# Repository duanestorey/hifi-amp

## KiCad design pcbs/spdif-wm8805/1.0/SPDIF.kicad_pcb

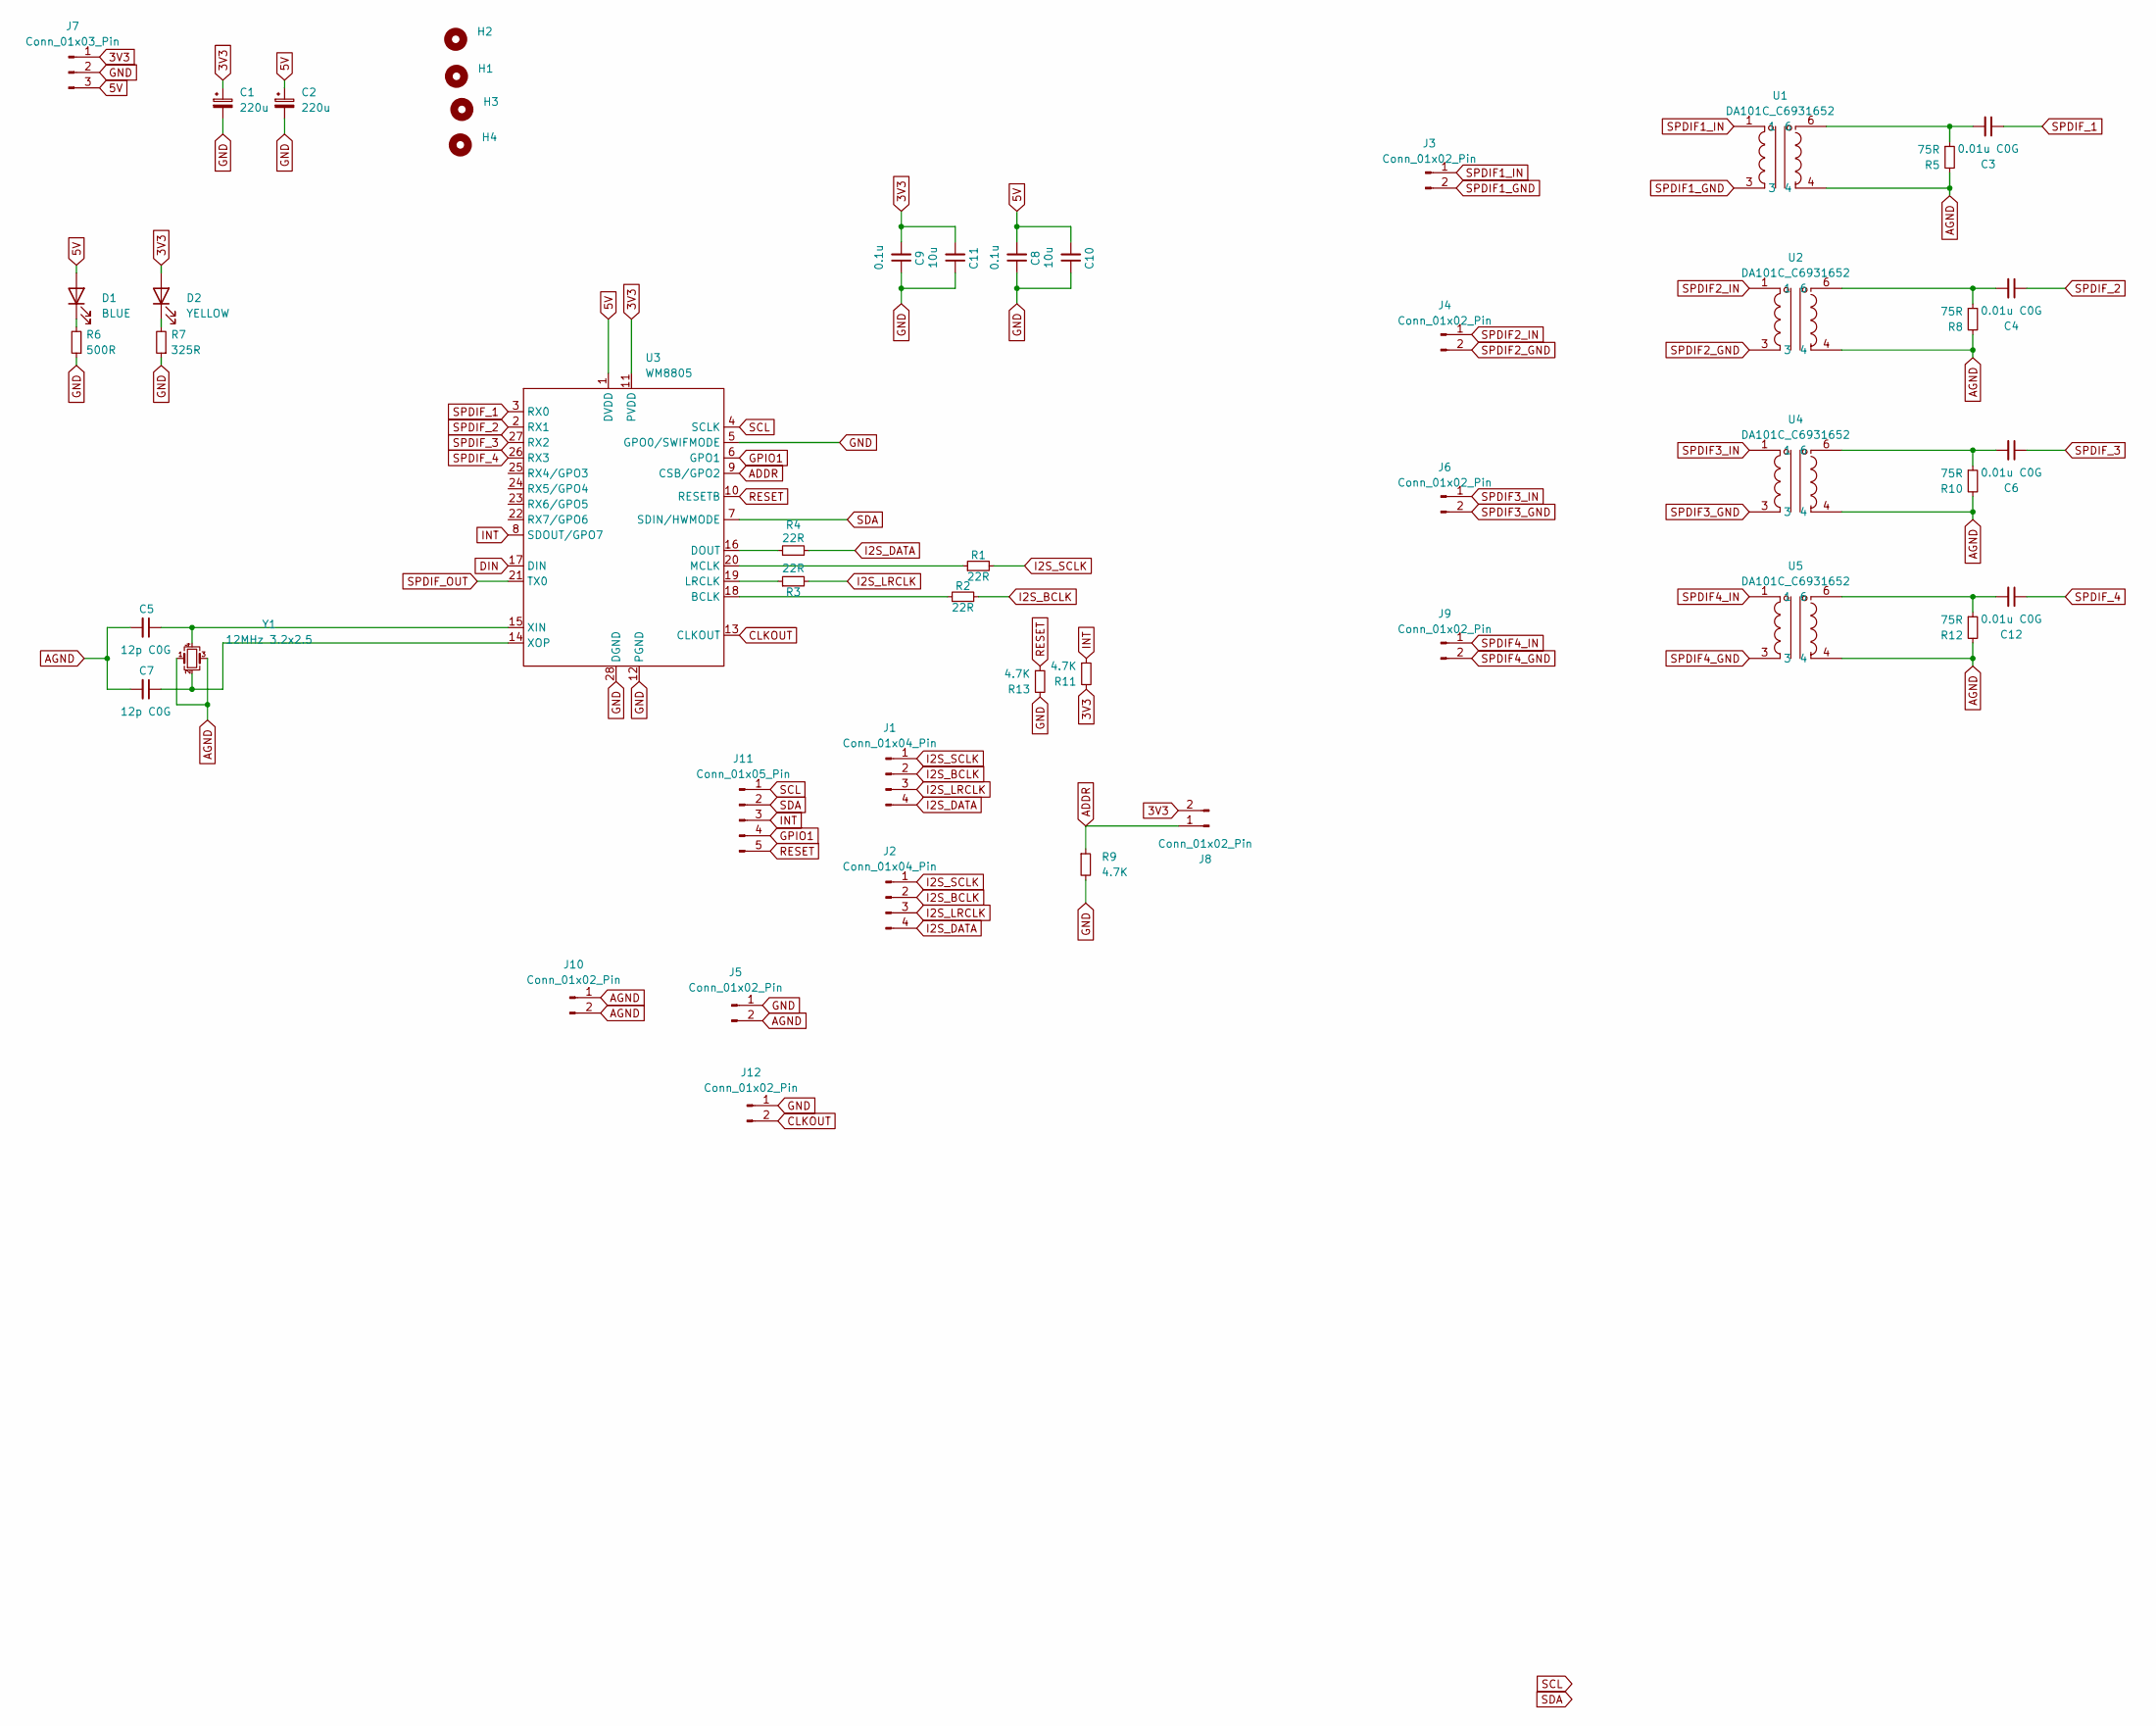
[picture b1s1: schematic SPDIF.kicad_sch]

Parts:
C1, C2: 220u; CP_Radial_D6.3mm_P2.50mm
C3, C4, C6, C12: 0.01u C0G; C_0805_2012Metric_Pad1.18x1.45mm_HandSolder; Mouser 791-0805N103G250CT
C5, C7: 12p C0G; C_0805_2012Metric_Pad1.18x1.45mm_HandSolder; Mouser 603-CC805FRNPO9BN120
C8, C9: 0.1u; C_0805_2012Metric_Pad1.18x1.45mm_HandSolder
C10, C11: 10u; C_1206_3216Metric_Pad1.33x1.80mm_HandSolder
D1: BLUE; LED_0805_2012Metric_Pad1.15x1.40mm_HandSolder
D2: YELLOW; LED_0805_2012Metric_Pad1.15x1.40mm_HandSolder
H1, H2, H3, H4: MountingHole; MountingHole_3.2mm_M3_DIN965_Pad_TopOnly
J1: Conn_01x04_Pin; JST_PH_B4B-PH-K_1x04_P2.00mm_Vertical
J2: Conn_01x04_Pin; PinHeader_1x04_P2.54mm_Vertical
J3, J4, J6, J9: Conn_01x02_Pin; JST_XH_B2B-XH-A_1x02_P2.50mm_Vertical
J5, J8, J12: Conn_01x02_Pin; PinHeader_1x02_P2.54mm_Vertical
J7: Conn_01x03_Pin; JST_PH_B3B-PH-K_1x03_P2.00mm_Vertical
J10: Conn_01x02_Pin; JST_PH_B2B-PH-K_1x02_P2.00mm_Vertical
J11: Conn_01x05_Pin; JST_PH_B5B-PH-K_1x05_P2.00mm_Vertical
R1, R2, R3, R4: 22R; R_0805_2012Metric_Pad1.20x1.40mm_HandSolder
R5, R8, R10, R12: 75R; R_0805_2012Metric_Pad1.20x1.40mm_HandSolder; Mouser 71-CRCW0603-75-E3
R6: 500R; R_0603_1608Metric_Pad0.98x0.95mm_HandSolder
R7: 325R; R_0603_1608Metric_Pad0.98x0.95mm_HandSolder
R9, R11, R13: 4.7K; R_0603_1608Metric_Pad0.98x0.95mm_HandSolder
U1, U2, U4, U5: DA101C_C6931652; XFMR-TH_4P-L9.5-W9.0-P5.08-LS10.2_C9900096976; LCSC Part C6931652
U3: WM8805; SSOP-28_5.3x10.2mm_P0.65mm
Y1: 12MHz 3.2x2.5; Crystal_SMD_SeikoEpson_FA238-4Pin_3.2x2.5mm_HandSoldering; Mouser 520-120-8-33B2CKMTR3

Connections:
3V3: C1.1, C9.2, C11.2, D2.2 (A), J7.1, J8.2, R11.2, U3.11 (PVDD)
5V: C2.1, C8.2, C10.2, D1.2 (A), J7.3, U3.1 (DVDD)
ADDR: J8.1, R9.1, U3.9 (CSB/GPO2)
AGND: C5.2, C7.2, J5.2, J10.1, J10.2, R5.2, R8.2, R10.2, R12.2, U1.4, U2.4, U4.4, U5.4, Y1.1, Y1.3
CLKOUT: J12.2, U3.13 (CLKOUT)
DIN: U3.17 (DIN)
GND: C1.2, C2.2, C8.1, C9.1, C10.1, C11.1, J5.1, J7.2, J12.1, R6.1, R7.1, R9.2, R13.2, U3.5 (GPO0/SWIFMODE), U3.12 (PGND), U3.28 (DGND)
GPIO1: J11.4, U3.6 (GPO1)
I2S_BCLK: J1.2, J2.2, R2.2
I2S_DATA: J1.4, J2.4, R4.2
I2S_LRCLK: J1.3, J2.3, R3.2
I2S_SCLK: J1.1, J2.1, R1.2
INT: J11.3, R11.1, U3.8 (SDOUT/GPO7)
unnamed: C3.2, R5.1, U1.6
unnamed: C4.2, R8.1, U2.6
unnamed: C6.2, R10.1, U4.6
unnamed: C12.2, R12.1, U5.6
unnamed: D1.1 (K), R6.2
unnamed: D2.1 (K), R7.2
unnamed: R2.1, U3.18 (BCLK)
unnamed: R4.1, U3.16 (DOUT)
unnamed: R3.1, U3.19 (LRCLK)
unnamed: R1.1, U3.20 (MCLK)
unnamed: C5.1, U3.15 (XIN), Y1.4
unnamed: C7.1, U3.14 (XOP), Y1.2
RESET: J11.5, R13.1, U3.10 (RESETB)
SCL: J11.1, U3.4 (SCLK)
SDA: J11.2, U3.7 (SDIN/HWMODE)
SPDIF1_GND: J3.2, U1.3
SPDIF1_IN: J3.1, U1.1
SPDIF2_GND: J4.2, U2.3
SPDIF2_IN: J4.1, U2.1
SPDIF3_GND: J6.2, U4.3
SPDIF3_IN: J6.1, U4.1
SPDIF4_GND: J9.2, U5.3
SPDIF4_IN: J9.1, U5.1
SPDIF_1: C3.1, U3.3 (RX0)
SPDIF_2: C4.1, U3.2 (RX1)
SPDIF_3: C6.1, U3.27 (RX2)
SPDIF_4: C12.1, U3.26 (RX3)
SPDIF_OUT: U3.21 (TX0)

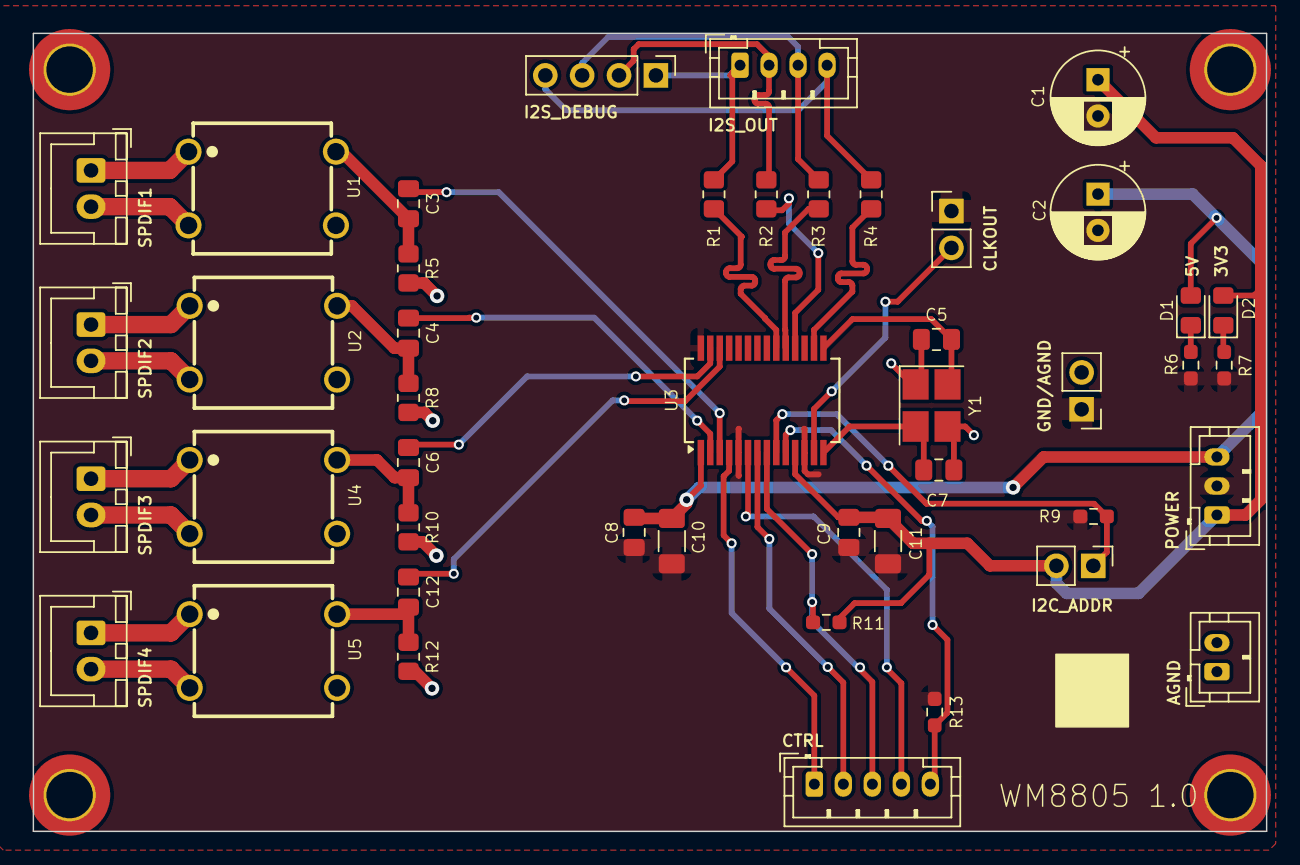
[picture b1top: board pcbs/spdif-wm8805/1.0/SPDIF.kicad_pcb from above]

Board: 2 copper layers, 85.0 x 55.0 mm, 49 parts (0 on the bottom side), 39 nets.

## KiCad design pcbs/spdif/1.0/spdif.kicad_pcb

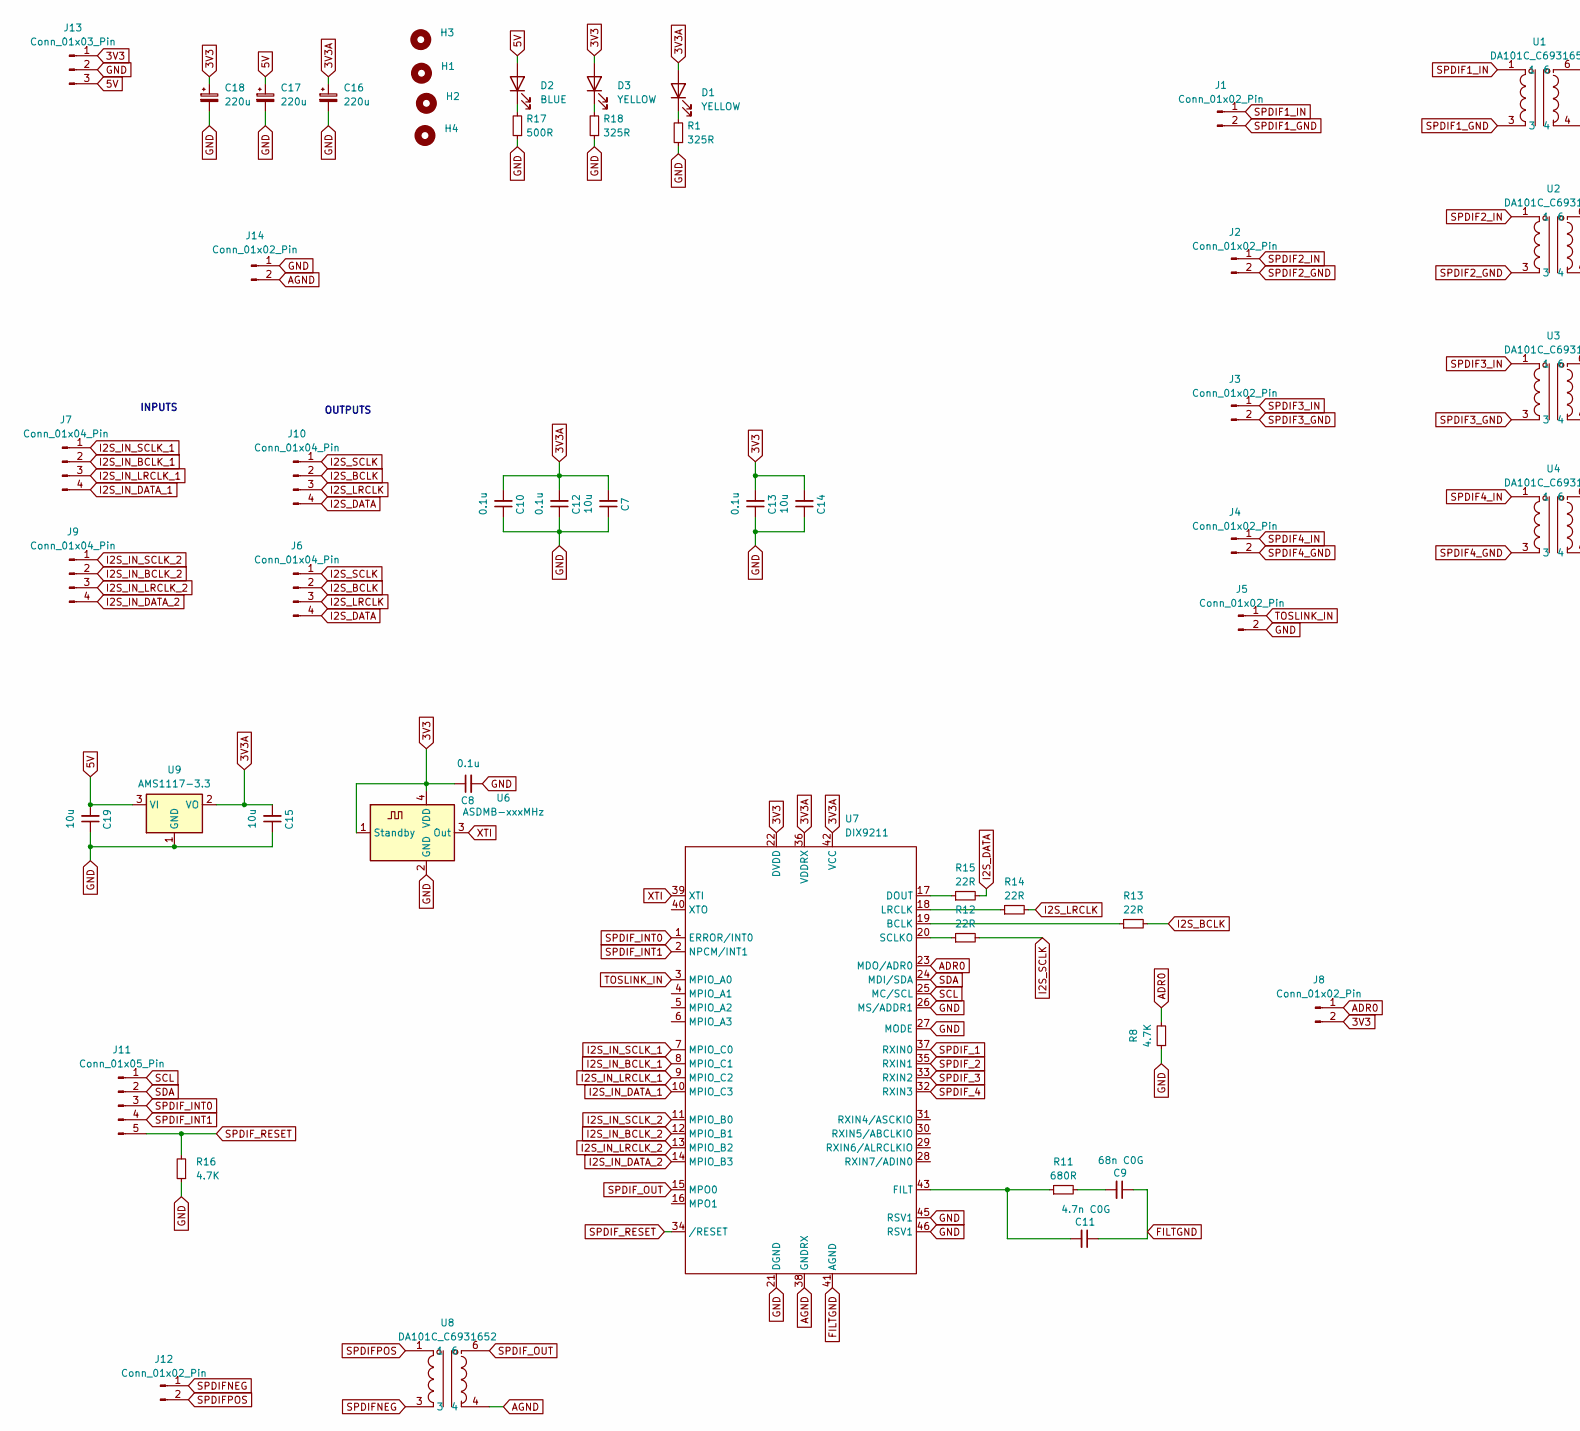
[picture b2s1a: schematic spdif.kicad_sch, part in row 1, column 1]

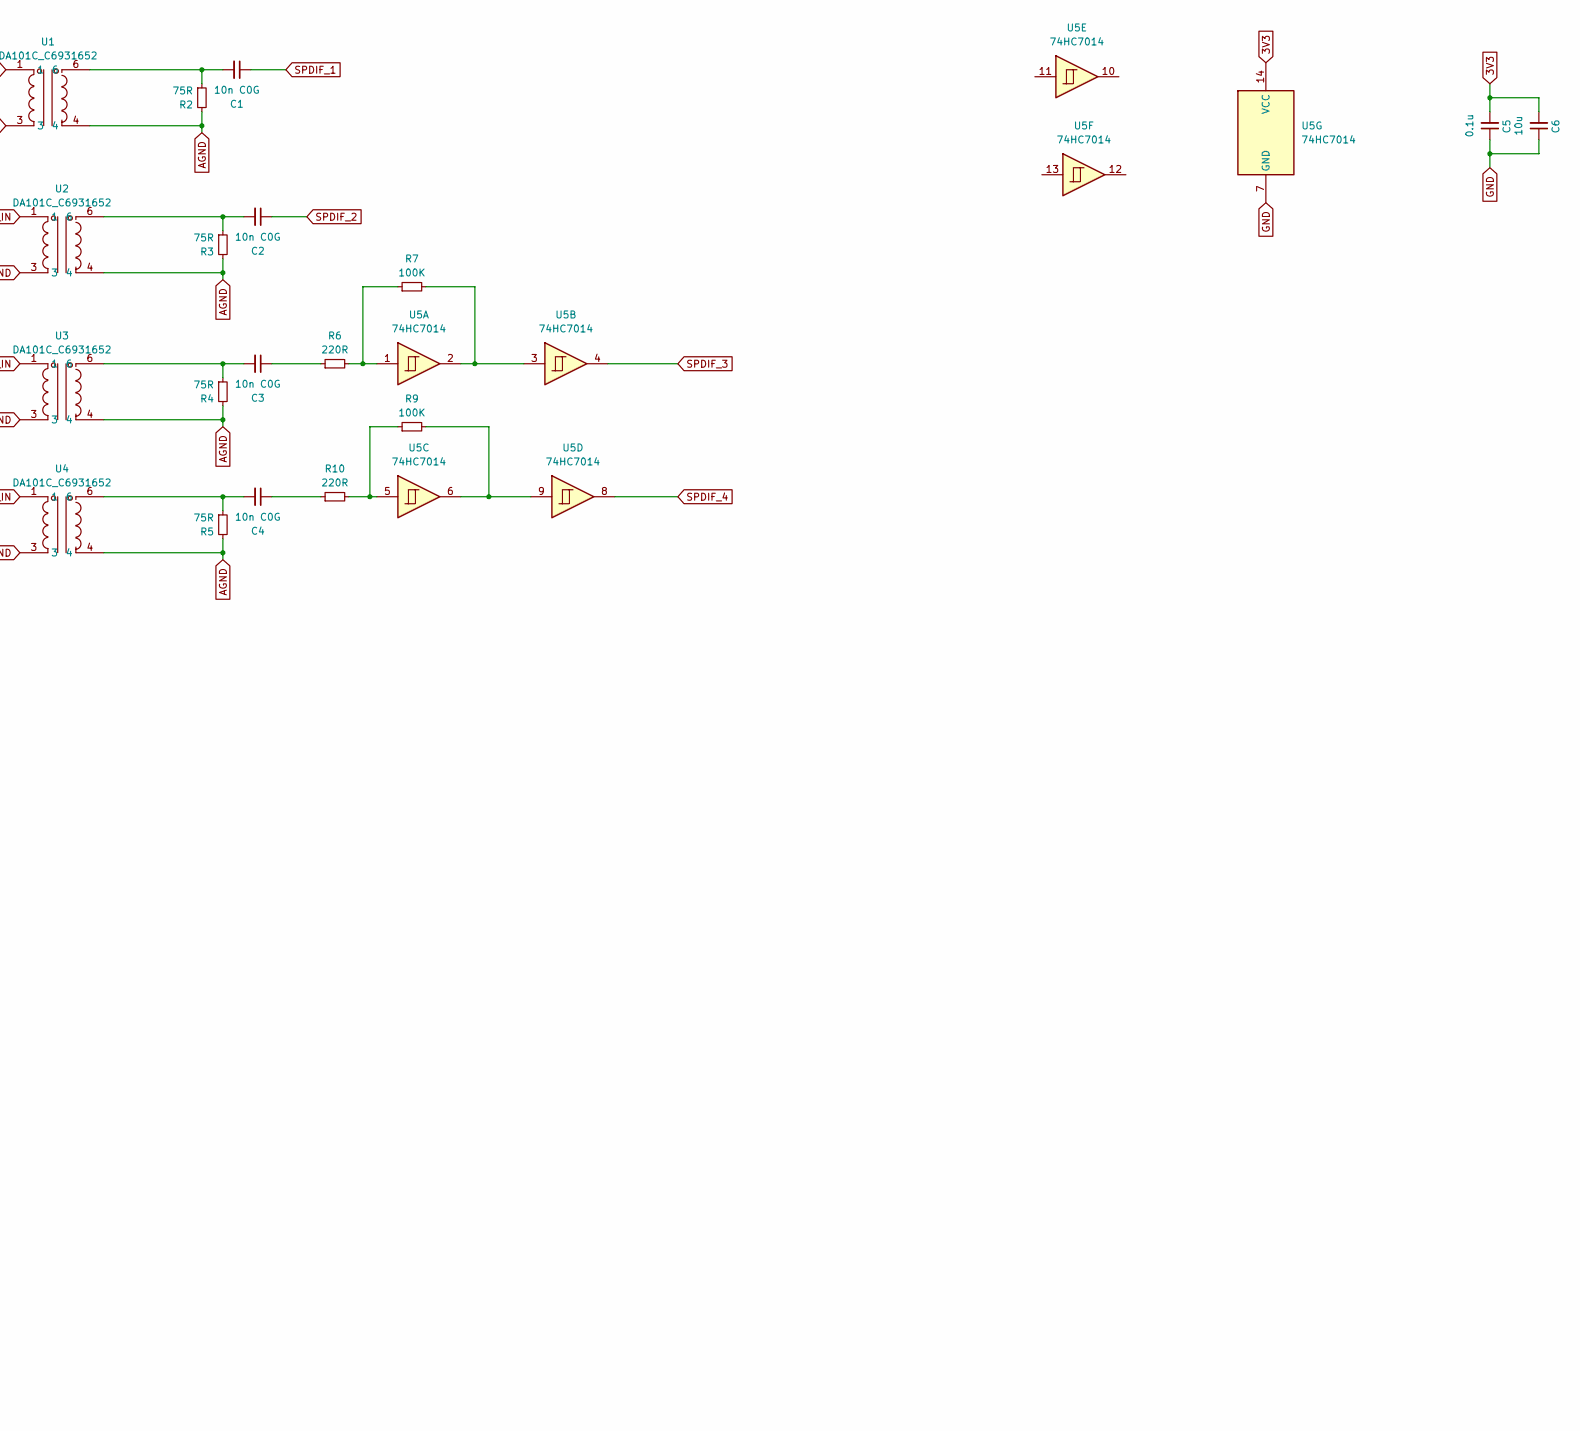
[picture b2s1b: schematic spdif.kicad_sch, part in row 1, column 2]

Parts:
C1, C2, C3, C4: 10n C0G; C_0805_2012Metric_Pad1.18x1.45mm_HandSolder; Mouser 791-0805N103G250CT
C5, C8, C10, C12, C13: 0.1u; C_0805_2012Metric_Pad1.18x1.45mm_HandSolder
C6, C7, C14, C15, C19: 10u; C_1206_3216Metric_Pad1.33x1.80mm_HandSolder
C9: 68n C0G; C_1206_3216Metric; Mouser 81-GRM3195C1H683JA5D
C11: 4.7n C0G; C_0603_1608Metric; Mouser 791-0603N472F500CT
C16, C17, C18: 220u; CP_Radial_D6.3mm_P2.50mm
D1, D3: YELLOW; LED_0603_1608Metric
D2: BLUE; LED_0603_1608Metric
H1, H2, H3, H4: MountingHole; MountingHole_3.2mm_M3_DIN965_Pad_TopOnly
J1, J2, J3, J4, J5, J12: Conn_01x02_Pin; JST_XH_B2B-XH-A_1x02_P2.50mm_Vertical
J6: Conn_01x04_Pin; PinHeader_1x04_P2.54mm_Vertical
J7, J9, J10: Conn_01x04_Pin; JST_PH_B4B-PH-K_1x04_P2.00mm_Vertical
J8, J14: Conn_01x02_Pin; PinHeader_1x02_P2.54mm_Vertical
J11: Conn_01x05_Pin; JST_PH_B5B-PH-K_1x05_P2.00mm_Vertical
J13: Conn_01x03_Pin; JST_PH_B3B-PH-K_1x03_P2.00mm_Vertical
R1, R18: 325R; R_0603_1608Metric_Pad0.98x0.95mm_HandSolder
R2, R3, R4, R5: 75R; R_0603_1608Metric_Pad0.98x0.95mm_HandSolder; Mouser 71-CRCW0603-75-E3
R6, R10: 220R; R_0603_1608Metric_Pad0.98x0.95mm_HandSolder; Mouser 71-CRCW0603-75-E3
R7, R9: 100K; R_0603_1608Metric_Pad0.98x0.95mm_HandSolder; Mouser 71-CRCW0603-75-E3
R8, R16: 4.7K; R_0603_1608Metric
R11: 680R; R_0603_1608Metric; Mouser 603-RT0603FRE07680RL
R12: 22R; R_0805_2012Metric
R13, R14, R15: 22R; R_0805_2012Metric; Mouser 603-RT0805FRE0722RL
R17: 500R; R_0603_1608Metric_Pad0.98x0.95mm_HandSolder
U1, U2, U3, U4, U8: DA101C_C6931652; XFMR-TH_4P-L9.5-W9.0-P5.08-LS10.2_C9900096976; LCSC Part C6931652
U5: 74HC7014; TSSOP-14_4.4x5mm_P0.65mm; Mouser 771-74HC7014D-T
U6: ASDMB-xxxMHz; Oscillator_SMD_Abracon_ASE-4Pin_3.2x2.5mm; Mouser 346-3225Z24.5760C1KX
U7: DIX9211; LQFP-48_7x7mm_P0.5mm; Mouser 595-DIX9211PTR
U9: AMS1117-3.3; SOT-223-3_TabPin2

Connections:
3V3: C5.2, C6.2, C8.1, C13.2, C14.2, C18.1, D3.2 (A), J8.2, J13.1, U5.14 (VCC), U6.1 (Standby), U6.4 (VDD), U7.22 (DVDD)
3V3A: C7.2, C10.2, C12.2, C15.2, C16.1, D1.2 (A), U7.36 (VDDRX), U7.42 (VCC), U9.2 (VO)
5V: C17.1, C19.2, D2.2 (A), J13.3, U9.3 (VI)
ADR0: J8.1, R8.2, U7.23 (MDO/ADR0)
AGND: J14.2, R2.2, R3.2, R4.2, R5.2, U1.4, U2.4, U3.4, U4.4, U7.38 (GNDRX), U8.4
FILTGND: C9.1, C11.1, U7.41 (AGND)
GND: C5.1, C6.1, C7.1, C8.2, C10.1, C12.1, C13.1, C14.1, C15.1, C16.2, C17.2, C18.2, C19.1, J5.2, J13.2, J14.1, R1.1, R8.1, R16.1, R17.1, R18.1, U5.7 (GND), U6.2 (GND), U7.21 (DGND), U7.26 (MS/ADDR1), U7.27 (MODE), U7.45 (RSV1), U7.46 (RSV1), U9.1 (GND)
I2S_BCLK: J6.2, J10.2, R13.2
I2S_DATA: J6.4, J10.4, R15.2
I2S_IN_BCLK_1: J7.2, U7.8 (MPIO_C1)
I2S_IN_BCLK_2: J9.2, U7.12 (MPIO_B1)
I2S_IN_DATA_1: J7.4, U7.10 (MPIO_C3)
I2S_IN_DATA_2: J9.4, U7.14 (MPIO_B3)
I2S_IN_LRCLK_1: J7.3, U7.9 (MPIO_C2)
I2S_IN_LRCLK_2: J9.3, U7.13 (MPIO_B2)
I2S_IN_SCLK_1: J7.1, U7.7 (MPIO_C0)
I2S_IN_SCLK_2: J9.1, U7.11 (MPIO_B0)
I2S_LRCLK: J6.3, J10.3, R14.2
I2S_SCLK: J6.1, J10.1, R12.2
unnamed: C1.2, R2.1, U1.6
unnamed: C2.2, R3.1, U2.6
unnamed: C3.1, R6.1
unnamed: C3.2, R4.1, U3.6
unnamed: C4.1, R10.1
unnamed: C4.2, R5.1, U4.6
unnamed: C9.2, R11.2
unnamed: D1.1 (K), R1.2
unnamed: D2.1 (K), R17.2
unnamed: D3.1 (K), R18.2
unnamed: R6.2, R7.1, U5.1
unnamed: R7.2, U5.2, U5.3
unnamed: R9.2, U5.6, U5.9
unnamed: R9.1, R10.2, U5.5
unnamed: R13.1, U7.19 (BCLK)
unnamed: R15.1, U7.17 (DOUT)
unnamed: C11.2, R11.1, U7.43 (FILT)
unnamed: R14.1, U7.18 (LRCLK)
unnamed: R12.1, U7.20 (SCLKO)
SCL: J11.1, U7.25 (MC/SCL)
SDA: J11.2, U7.24 (MDI/SDA)
SPDIF1_GND: J1.2, U1.3
SPDIF1_IN: J1.1, U1.1
SPDIF2_GND: J2.2, U2.3
SPDIF2_IN: J2.1, U2.1
SPDIF3_GND: J3.2, U3.3
SPDIF3_IN: J3.1, U3.1
SPDIF4_GND: J4.2, U4.3
SPDIF4_IN: J4.1, U4.1
SPDIFNEG: J12.1, U8.3
SPDIFPOS: J12.2, U8.1
SPDIF_1: C1.1, U7.37 (RXIN0)
SPDIF_2: C2.1, U7.35 (RXIN1)
SPDIF_3: U5.4, U7.33 (RXIN2)
SPDIF_4: U5.8, U7.32 (RXIN3)
SPDIF_INT0: J11.3, U7.1 (ERROR/INT0)
SPDIF_INT1: J11.4, U7.2 (NPCM/INT1)
SPDIF_OUT: U7.15 (MPO0), U8.6
SPDIF_RESET: J11.5, R16.2, U7.34 (/RESET)
TOSLINK_IN: J5.1, U7.3 (MPIO_A0)
XTI: U6.3 (Out), U7.39 (XTI)

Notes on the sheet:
OUTPUTS
INPUTS

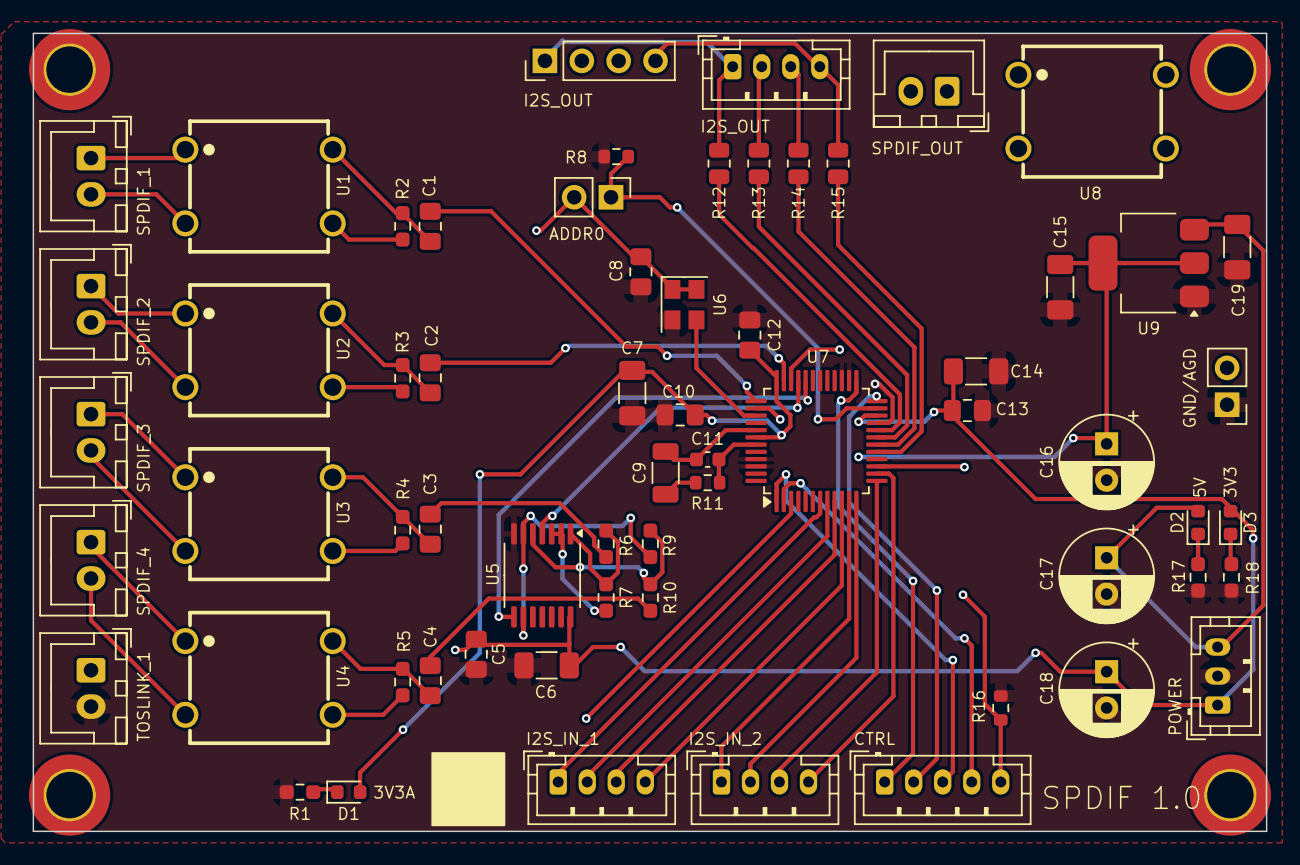
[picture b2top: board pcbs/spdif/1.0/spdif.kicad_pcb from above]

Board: 4 copper layers, 85.0 x 55.0 mm, 67 parts (0 on the bottom side), 60 nets.

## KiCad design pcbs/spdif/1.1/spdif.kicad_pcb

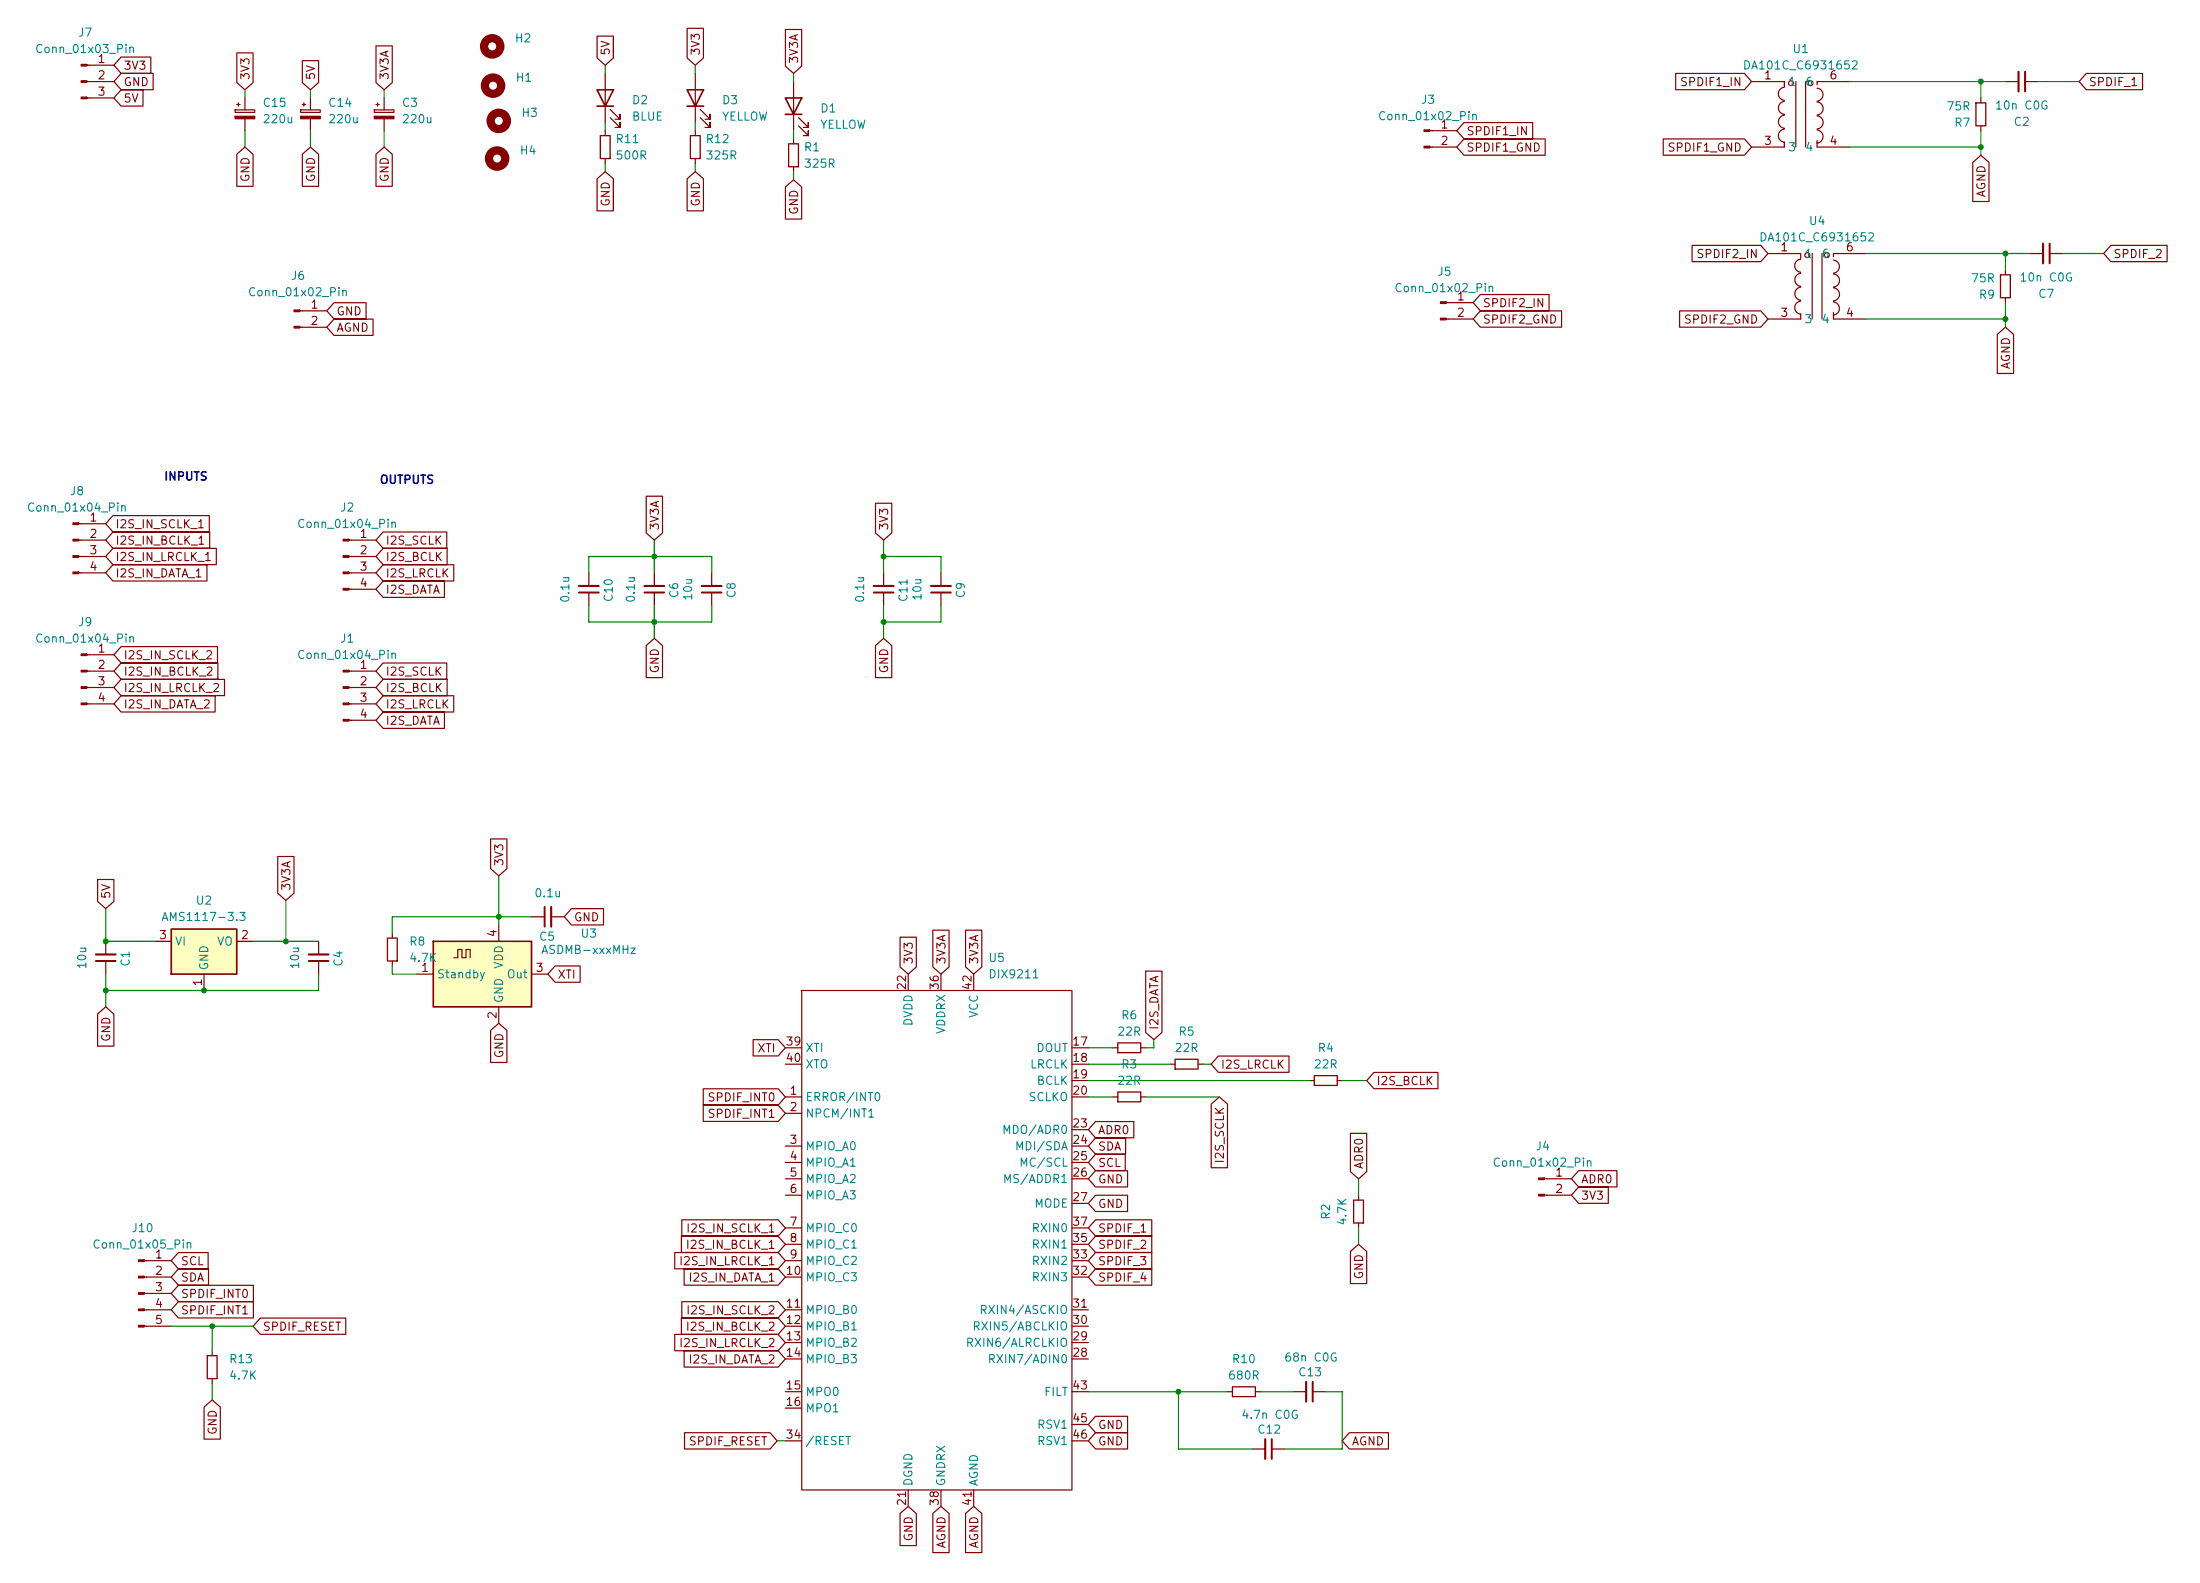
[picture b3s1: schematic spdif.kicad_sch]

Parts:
C1, C4, C8, C9: 10u; C_1206_3216Metric_Pad1.33x1.80mm_HandSolder
C2, C7: 10n C0G; C_0805_2012Metric_Pad1.18x1.45mm_HandSolder; Mouser 791-0805N103G250CT
C3, C14, C15: 220u; CP_Radial_D6.3mm_P2.50mm
C5, C6, C10, C11: 0.1u; C_0805_2012Metric_Pad1.18x1.45mm_HandSolder
C12: 4.7n C0G; C_0603_1608Metric; Mouser 791-0603N472F500CT
C13: 68n C0G; C_1206_3216Metric; Mouser 81-GRM3195C1H683JA5D
D1, D3: YELLOW; LED_0603_1608Metric
D2: BLUE; LED_0603_1608Metric
H1, H2, H3, H4: MountingHole; MountingHole_3.2mm_M3_DIN965_Pad_TopOnly
J1: Conn_01x04_Pin; PinHeader_1x04_P2.54mm_Vertical
J2, J8, J9: Conn_01x04_Pin; JST_PH_B4B-PH-K_1x04_P2.00mm_Vertical
J3, J5: Conn_01x02_Pin; JST_XH_B2B-XH-A_1x02_P2.50mm_Vertical
J4, J6: Conn_01x02_Pin; PinHeader_1x02_P2.54mm_Vertical
J7: Conn_01x03_Pin; JST_PH_B3B-PH-K_1x03_P2.00mm_Vertical
J10: Conn_01x05_Pin; JST_PH_B5B-PH-K_1x05_P2.00mm_Vertical
R1, R12: 325R; R_0603_1608Metric_Pad0.98x0.95mm_HandSolder
R2, R8, R13: 4.7K; R_0603_1608Metric
R3: 22R; R_0805_2012Metric
R4, R5, R6: 22R; R_0805_2012Metric; Mouser 603-RT0805FRE0722RL
R7, R9: 75R; R_0603_1608Metric_Pad0.98x0.95mm_HandSolder; Mouser 71-CRCW0603-75-E3
R10: 680R; R_0603_1608Metric; Mouser 603-RT0603FRE07680RL
R11: 500R; R_0603_1608Metric_Pad0.98x0.95mm_HandSolder
U1, U4: DA101C_C6931652; XFMR-TH_4P-L9.5-W9.0-P5.08-LS10.2_C9900096976; LCSC Part C6931652
U2: AMS1117-3.3; SOT-223-3_TabPin2
U3: ASDMB-xxxMHz; Oscillator_SMD_Abracon_ASE-4Pin_3.2x2.5mm; Mouser 346-3225Z24.5760C1KX
U5: DIX9211; LQFP-48_7x7mm_P0.5mm; Mouser 595-DIX9211PTR

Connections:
3V3: C5.1, C9.2, C11.2, C15.1, D3.2 (A), J4.2, J7.1, R8.2, U3.4 (VDD), U5.22 (DVDD)
3V3A: C3.1, C4.2, C6.2, C8.2, C10.2, D1.2 (A), U2.2 (VO), U5.36 (VDDRX), U5.42 (VCC)
5V: C1.2, C14.1, D2.2 (A), J7.3, U2.3 (VI)
ADR0: J4.1, R2.2, U5.23 (MDO/ADR0)
AGND: C12.1, C13.1, J6.2, R7.2, R9.2, U1.4, U4.4, U5.38 (GNDRX), U5.41 (AGND)
GND: C1.1, C3.2, C4.1, C5.2, C6.1, C8.1, C9.1, C10.1, C11.1, C14.2, C15.2, J6.1, J7.2, R1.1, R2.1, R11.1, R12.1, R13.1, U2.1 (GND), U3.2 (GND), U5.21 (DGND), U5.26 (MS/ADDR1), U5.27 (MODE), U5.45 (RSV1), U5.46 (RSV1)
I2S_BCLK: J1.2, J2.2, R4.2
I2S_DATA: J1.4, J2.4, R6.2
I2S_IN_BCLK_1: J8.2, U5.8 (MPIO_C1)
I2S_IN_BCLK_2: J9.2, U5.12 (MPIO_B1)
I2S_IN_DATA_1: J8.4, U5.10 (MPIO_C3)
I2S_IN_DATA_2: J9.4, U5.14 (MPIO_B3)
I2S_IN_LRCLK_1: J8.3, U5.9 (MPIO_C2)
I2S_IN_LRCLK_2: J9.3, U5.13 (MPIO_B2)
I2S_IN_SCLK_1: J8.1, U5.7 (MPIO_C0)
I2S_IN_SCLK_2: J9.1, U5.11 (MPIO_B0)
I2S_LRCLK: J1.3, J2.3, R5.2
I2S_SCLK: J1.1, J2.1, R3.2
unnamed: C2.2, R7.1, U1.6
unnamed: C7.2, R9.1, U4.6
unnamed: C13.2, R10.2
unnamed: D1.1 (K), R1.2
unnamed: D2.1 (K), R11.2
unnamed: D3.1 (K), R12.2
unnamed: R8.1, U3.1 (Standby)
unnamed: R4.1, U5.19 (BCLK)
unnamed: R6.1, U5.17 (DOUT)
unnamed: C12.2, R10.1, U5.43 (FILT)
unnamed: R5.1, U5.18 (LRCLK)
unnamed: R3.1, U5.20 (SCLKO)
SCL: J10.1, U5.25 (MC/SCL)
SDA: J10.2, U5.24 (MDI/SDA)
SPDIF1_GND: J3.2, U1.3
SPDIF1_IN: J3.1, U1.1
SPDIF2_GND: J5.2, U4.3
SPDIF2_IN: J5.1, U4.1
SPDIF_1: C2.1, U5.37 (RXIN0)
SPDIF_2: C7.1, U5.35 (RXIN1)
SPDIF_3: U5.33 (RXIN2)
SPDIF_4: U5.32 (RXIN3)
SPDIF_INT0: J10.3, U5.1 (ERROR/INT0)
SPDIF_INT1: J10.4, U5.2 (NPCM/INT1)
SPDIF_RESET: J10.5, R13.2, U5.34 (/RESET)
XTI: U3.3 (Out), U5.39 (XTI)

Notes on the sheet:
OUTPUTS
INPUTS

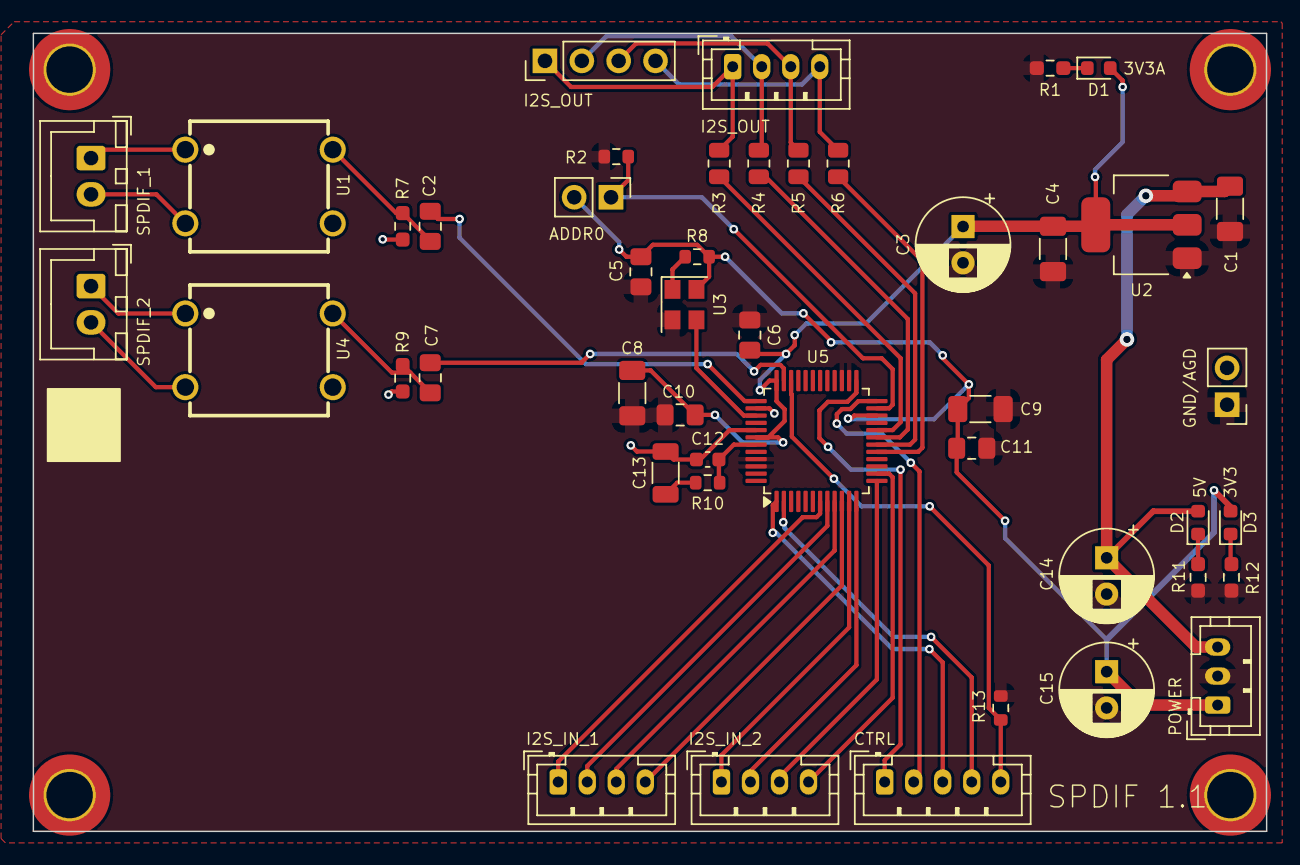
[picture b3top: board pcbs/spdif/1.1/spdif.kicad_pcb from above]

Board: 2 copper layers, 85.0 x 55.0 mm, 50 parts (0 on the bottom side), 42 nets.

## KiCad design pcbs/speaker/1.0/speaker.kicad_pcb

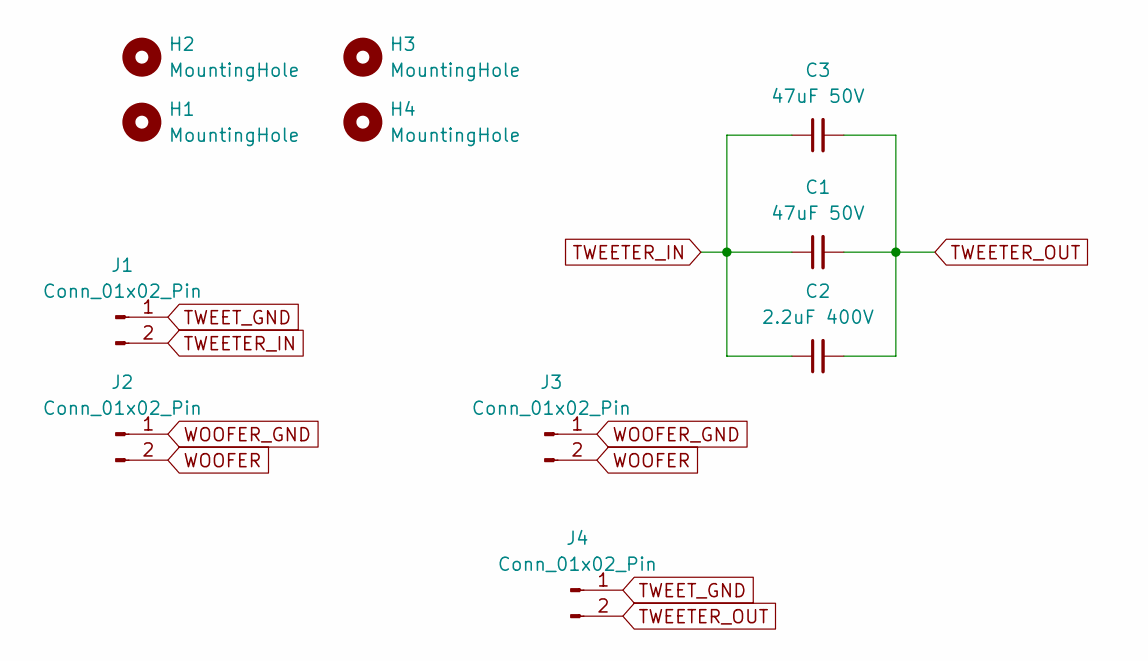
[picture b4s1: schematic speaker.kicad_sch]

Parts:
C1: 47uF 50V; CP_Radial_D10.0mm_P5.00mm_P7.50mm
C2: 2.2uF 400V; C_Rect_L31.5mm_W15.0mm_P27.50mm_MKS4
C3: 47uF 50V; CP_Radial_D6.3mm_P2.50mm
H1, H2, H3, H4: MountingHole; MountingHole_3.2mm_M3_DIN965_Pad_TopBottom
J1, J2, J3, J4: Conn_01x02_Pin; JST_VH_B2P-VH-B_1x02_P3.96mm_Vertical

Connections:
TWEETER_IN: C1.1, C2.1, C3.1, J1.2
TWEETER_OUT: C1.2, C2.2, C3.2, J4.2
TWEET_GND: J1.1, J4.1
WOOFER: J2.2, J3.2
WOOFER_GND: J2.1, J3.1
